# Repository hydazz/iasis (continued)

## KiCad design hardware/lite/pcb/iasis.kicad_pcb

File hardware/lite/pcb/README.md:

# Iasis board

KiCad 10 project for the six-layer, 133 × 102 mm Iasis board. One layout carries three assembly variants, Hub, HubPD and CM5; the [repository README](../../../README.md) describes them.

## Files

- `iasis.kicad_sch` and its sheets, `iasis.kicad_pcb`, `iasis.kicad_pro`, and `iasis.kicad_dru` for the rules the board setup cannot express.
- `Iasis.kicad_sym`, `Iasis.pretty` and `Iasis.3dshapes`: project symbols, footprints and models. `NOTICE` files give their sources and licences.
- `jlc_cpl.py` corrects placements for JLCPCB (below); `preview.py` writes `preview/board.png` and `preview/layout.png`; `diff.py` shows a board change (below).

## Fab files

Tools come from mise (`mise install` at the repository root); KiCad 10 must be at the path `KICAD_CLI` names in `.mise/config.toml`.

```bash
mise run //hardware/lite/pcb:fab
```

The task writes `build/`:

| File                           | Contents                                                  |
| ------------------------------ | --------------------------------------------------------- |
| `gerbers.zip`                  | Gerber and drill files                                    |
| `bom-Hub.csv`, `bom-HubPD.csv`, `bom-CM5.csv` | Bill of materials per variant, one row per LCSC part      |
| `cpl-Hub.csv`, `cpl-HubPD.csv`, `cpl-CM5.csv` | Placements per variant, corrected for JLCPCB's footprints |

Run `mise run //hardware/lite/pcb:preview` to refresh the tracked board and copper-layout images. Commit them with the design changes they show.

Run `mise run //hardware/lite/pcb:step` to export `build/board.step`, which the case tasks consume. Run `mise run //hardware/lite/pcb:check` for DRC with schematic parity and ERC errors; reports are written to `build/drc.json` and `build/erc.json`.

The upload ZIP contains Gerber and drill files. It excludes the optional Gerber job file, whose board-preview colour and impedance-control metadata differ from the order settings below.

The underside carries the name, repository URL and `REV ${REVISION}`, read from the board's title block. The PCB revision identifies a fabricated board design; tag its source commit (for example, `hw-rev-a`) and keep that release's fabrication files together. All three assembly variants share the PCB revision.

### Logo

Supply a filled SVG to place a logo on the back silkscreen:

```bash
mise run //hardware/lite/pcb:fab -- --logo ../../../logos/logo.svg
```

The logo fits within a 45 × 45 mm slot centred 82 mm from the left and 42.5 mm from the top, viewed from below. Its proportions and viewing orientation are preserved. Use solid filled paths; convert text and strokes to paths before exporting the SVG. KiCad's bundled Python, selected by `KICAD_PYTHON`, handles the import.

Without `--logo`, the board has only its identity text. The source board is never modified. Outputs include a board copy, project settings and `bottom.svg` alongside the fabrication files. Use `--output DIR` to change the output directory.

The root `logos/` directory holds local SVG inputs and ignores them by default. A logo can also be supplied from any other path.

## Visual diff

```bash
mise run //hardware/lite/pcb:diff
```

compares the last commit's board with the working copy; `diff REV` compares a revision with the working copy, and `diff OLD NEW` two revisions. The task plots each copper, silkscreen and courtyard layer and the outline of both boards, without zone fills, and draws what was removed red, what was added green and the rest grey. It opens `build/diff/index.html`, which pans and zooms each layer and counts the tracks, vias and footprints that changed.

## JLCPCB order

PCB options:

| Option                  | Setting                 | Reason                                                                                                        |
| ----------------------- | ----------------------- | ------------------------------------------------------------------------------------------------------------- |
| Layers, size            | 6, 133 × 102 mm          |                                                                                                               |
| Thickness               | 1.6 mm                  | Economic assembly of six layers needs 1.6 mm, green and ENIG                                                  |
| Specify stackup         | JLC06161H-3313          | The 90 Ω pairs (0.1356 mm tracks, 0.1501 mm gap) are sized for it; accept JLC's 1.54 mm actual thickness note |
| Colour                  | Green                   | As thickness                                                                                                  |
| Surface finish          | ENIG                    | As thickness. JLC preselects OSP, which rules out Economic assembly, and has no HASL                          |
| Via covering            | Epoxy filled and capped | No charge on six layers; some vias sit in pads                                                                |
| Min via hole / diameter | 0.3 / (0.4/0.45) mm     | No hole is smaller; 0.2 mm holes add a small-via charge and force TG155 and a 4-wire Kelvin test              |
| Impedance control       | No requirement          | ±10 % control adds a charge and requires production-file confirmation                                         |
| Mark on PCB             | Remove mark             |                                                                                                               |

Assembly options: Economic PCBA, top side, tooling holes added by JLCPCB, Confirm Parts Placement on (JLC confirms on its own after 72 hours unless "Do not confirm automatically" is ticked), parts selected by customer. PCBA quantity can be 2 or all 5 boards.

Upload `gerbers.zip`, then the variant's BOM and CPL, and:

1. Tick the USB-C rows (J1001, J401–J901). JLC charges a small fee for these parts and leaves them unticked after every upload.
2. Check every row is matched, in stock and selectable; Economic cannot place a part JLC marks Standard Only. Replace such a part in the schematic and regenerate the files, rather than in JLC's table, so the BOM here stays the order's source.
3. In Component Placements, every part should sit on its pads, and JLC's Align should change nothing. A part that Align turns or moves needs an entry in `jlc_cpl.py`.
4. The closest customs description is Research/Education/DIY, Development Board (HS 847330).

## Placement corrections

JLCPCB places its own (EasyEDA) footprint for each LCSC part, with its origin at the CPL's Mid X/Y and turned by Rotation. `jlc_cpl.py` holds, by LCSC code, the turn to add and the EasyEDA origin's position in the KiCad footprint, wherever the two footprints differ.

For a new part, fetch its EasyEDA footprint from `https://easyeda.com/api/products/<LCSC>/components?version=6.4.19.5` (pads in 0.254 mm units, y down, origin at `dataStr.head`). Match its pads to the KiCad pads by number at each quarter turn, then record the turn and origin that fit. Two-terminal chip parts need no entry.

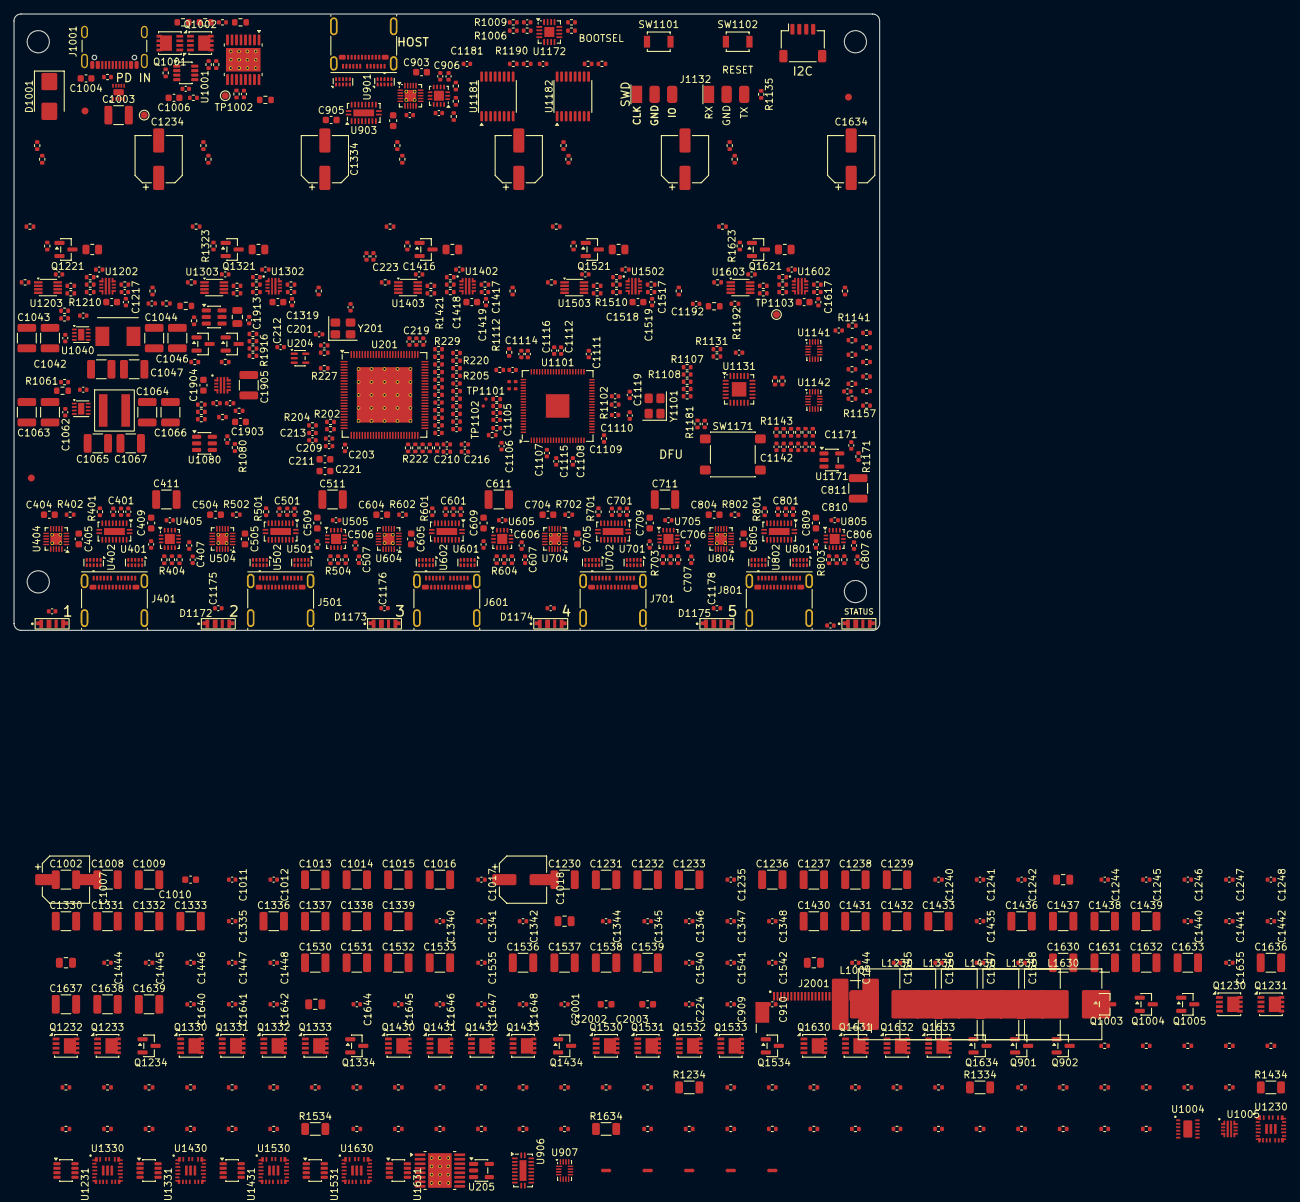
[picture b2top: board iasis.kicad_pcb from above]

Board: 6 copper layers, 125.0 x 89.0 mm, 718 parts (0 on the bottom side), 493 nets, no tracks yet.

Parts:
C201, C202, C1012: 33p C0G; C_0402_1005Metric
C203, C204, C205, C206, C207, C208, C209, C210, C212, C213, C214, C215, C216, C217, C218, C219, C220, C224, C226, C403, C408, C410, C503, C508, C510, C603, C608, C610, C703, C708, C710, C803, C808, C810, C904, C908, C909, C910, C1011, C1041, C1061, C1080, C1104, C1105, C1106, C1107, C1108, C1109, C1110, C1111, C1112, C1113, C1114, C1115, C1116, C1131, C1141, C1147, C1170, C1171, C1172, C1173, C1174, C1175, C1176, C1177, C1178, C1181, C1182, C1216, C1241, C1242, C1316, C1341, C1342, C1416, C1441, C1442, C1516, C1541, C1542, C1616, C1641, C1642, C1906, C1911, C1913: 100n; C_0402_1005Metric
C211, C221: 10u 10V; C_0603_1608Metric
C222, C223: 100n 16V X7R; C_0402_1005Metric
C401, C402, C501, C502, C601, C602, C701, C702, C801, C802: 100n 25V X7R; C_0402_1005Metric
C404, C409, C504, C509, C604, C609, C704, C709, C804, C809, C902, C905: 1u 10V X7R; C_0603_1608Metric
C405, C505, C605, C705, C805, C903: 100n 50V X7R; C_0603_1608Metric
C406, C407, C506, C507, C606, C607, C706, C707, C806, C807, C906, C907, C1060: 220p C0G; C_0402_1005Metric
C411, C511, C611, C711, C811, C1013, C1014, C1015, C1016, C1042, C1043, C1044, C1045, C1046, C1047, C1062, C1063, C1064, C1065, C1066, C1067, C1905: 22u 16V X7R; C_1210_3225Metric
C1001, C1005, C1219, C1220, C1235, C1240, C1247, C1248, C1319, C1320, C1335, C1340, C1347, C1348, C1419, C1420, C1435, C1440, C1447, C1448, C1519, C1520, C1535, C1540, C1547, C1548, C1619, C1620, C1635, C1640, C1647, C1648: 100n 50V X7R; C_0402_1005Metric
C1002, C1003, C1008, C1009, C1230, C1231, C1232, C1233, C1236, C1237, C1238, C1239, C1330, C1331, C1332, C1333, C1336, C1337, C1338, C1339, C1430, C1431, C1432, C1433, C1436, C1437, C1438, C1439, C1530, C1531, C1532, C1533, C1536, C1537, C1538, C1539, C1630, C1631, C1632, C1633, C1636, C1637, C1638, C1639: 10u 50V X7R; C_1210_3225Metric
C1004, C1010, C2002, C2003: 100n 100V X7R; C_0603_1608Metric
C1006: 22n 100V X7R; C_0603_1608Metric
C1007: 33u 50V; CP_Elec_6.3x7.7
C1017, C1040, C1245, C1345, C1445, C1545, C1645: 4.7n; C_0402_1005Metric
C1018, C1234, C1334, C1434, C1534, C1634: 100u 35V; CP_Elec_6.3x7.7
C1101, C1102: 4.7u 10V X5R; C_0402_1005Metric_WideGap
C1103, C1117: 4.7u 10V X5R; C_0402_1005Metric
C1118, C1119: 15p C0G; C_0402_1005Metric
C1142, C1143, C1144, C1145, C1146, C1148, C1191, C1192, C1244, C1344, C1444, C1544, C1644, C2001: 10n; C_0402_1005Metric
C1217, C1317, C1417, C1517, C1617: 1n 50V C0G; C_0402_1005Metric
C1218, C1318, C1418, C1518, C1618, C1904: 2.2u 25V X5R; C_0603_1608Metric
C1243, C1343, C1443, C1543, C1643, C1912: 10u 16V X5R; C_0805_2012Metric
C1246, C1346, C1446, C1546, C1646: 100p C0G; C_0402_1005Metric
C1903: 47n 50V X7R; C_0603_1608Metric
D1001: SMBJ30CA; D_SMB
D1170, D1171, D1172, D1173, D1174, D1175: SK6812SIDE-A; OPSCO_SK6812SIDE-A
FID1, FID2, FID3: Fiducial; Fiducial_1mm_Mask2mm
H1, H2, H3, H4: MountingHole_3.2mm_M3
J401, J501, J601, J701, J801, J901: 1054500101; USB_C_Receptacle_Molex_105450-0101
J1001: USB4105-GF-A-120; GCT_USB4105_GF_A_120
J1101: SWD debug; SolderPads_1x03_P2.54mm
J1131: SM04B-SRSS-TB; JST_SH_SM04B-SRSS-TB_1x04-1MP_P1.00mm_Horizontal
J1132: UART debug; SolderPads_1x03_P2.54mm
J2001: 05A20L24P; HanElectricity_05A20L24P
L1004: 6.8u 12.5A; PSTMAA666460
L1040: SRP5030CC-2R2M; Bourns_SRP5030CC
L1060: AAPS0530M1R0F; L_Coilank_AAPS0530
L1230, L1330, L1430, L1530, L1630: 4.7u; L_Changjiang_FXL1050
NT1230, NT1330, NT1430, NT1530, NT1630: NetTie_2; NetTie-2_SMD_Pad0.5mm
Q901, Q902, Q1003, Q1004, Q1005, Q1221, Q1234, Q1321, Q1334, Q1421, Q1434, Q1521, Q1534, Q1621, Q1634, Q1911, Q1912: 2N7002; SOT-23
Q1001, Q1002, Q1232, Q1233, Q1332, Q1333, Q1432, Q1433, Q1532, Q1533, Q1632, Q1633: SP60N05GNJ; Vishay_PowerPAK_1212-8_Single
Q1230, Q1231, Q1330, Q1331, Q1430, Q1431, Q1530, Q1531, Q1630, Q1631: TMGN4060DF; Vishay_PowerPAK_1212-8_Single
R201: 12k 1%; R_0402_1005Metric
R202, R1012, R1191, R1192, R1212, R1312, R1412, R1512, R1612, R1907: 10k 1%; R_0402_1005Metric
R203, R204, R205, R206, R232, R1235, R1335, R1435, R1535, R1635, R1913: 200k 1%; R_0402_1005Metric
R207, R208, R209, R210, R211, R212, R213, R214, R215, R401, R402, R403, R501, R502, R503, R601, R602, R603, R701, R702, R703, R801, R802, R803, R901, R907, R1006, R1009, R1015, R1020, R1022, R1024, R1080, R1104, R1112, R1135, R1173, R1181, R1187, R1210, R1310, R1410, R1510, R1610, R1912, R2003, R2005: 10k; R_0402_1005Metric
R217, R218, R219, R220, R221, R222, R223, R224, R225, R226, R227, R228, R229, R230, R231, R904, R906, R1010, R1026, R1029, R1172, R1185, R1188, R1189, R1190, R1209, R1214, R1215, R1221, R1223, R1238, R1239, R1309, R1314, R1315, R1321, R1323, R1338, R1339, R1409, R1414, R1415, R1421, R1423, R1438, R1439, R1509, R1514, R1515, R1521, R1523, R1538, R1539, R1609, R1614, R1615, R1621, R1623, R1638, R1639, R1911, R1915, R1917: 100k; R_0402_1005Metric
R404, R405, R504, R505, R604, R605, R704, R705, R804, R805, R902, R903, R1028, R1107, R1108, R1109, R1110, R1111, R1136, R1137: 4.7k; R_0402_1005Metric
R905: 1M; R_0402_1005Metric
R1001, R1002: 100k 0.1%; R_0603_1608Metric
R1003, R1014, R1021, R1231, R1232, R1236, R1331, R1332, R1336, R1431, R1432, R1436, R1531, R1532, R1536, R1631, R1632, R1636: 47k 1%; R_0402_1005Metric
R1004: 10k 0.1%; R_0603_1608Metric
R1005: 100k 1%; R_0402_1005Metric
R1007: 22; R_0603_1608Metric
R1008, R2002: 6.8k 1%; R_0402_1005Metric
R1011: 249k 1%; R_0402_1005Metric
R1013, R1102, R1103: 1k; R_0402_1005Metric
R1016: 120k 1%; R_0402_1005Metric
R1017, R1916: 22k 1%; R_0402_1005Metric
R1018, R1025, R1909: 1k 1%; R_0402_1005Metric
R1019, R1023, R1211, R1311, R1411, R1511, R1611: 39k 1%; R_0402_1005Metric
R1027, R1908: 20k 1%; R_0402_1005Metric
R1040, R1060, R1142, R1145, R1148, R1151, R1154, R1157: 10k 0.1%; R_0402_1005Metric
R1041: 2.2k 0.1%; R_0402_1005Metric
R1061: 11.3k 0.1%; R_0603_1608Metric
R1101, R1171: 33; R_0402_1005Metric
R1105, R1106: 27; R_0402_1005Metric
R1131, R1132: 2.2k; R_0402_1005Metric
R1141, R1144, R1147, R1150, R1153, R1156: 90.9k 0.1%; R_0402_1005Metric
R1143, R1146, R1149, R1152, R1155, R1158: 47k 0.1%; R_0402_1005Metric
R1213, R1313, R1413, R1513, R1613: 6.49k 1%; R_0402_1005Metric
R1222, R1322, R1422, R1522, R1622: 1k 1%; R_0805_2012Metric
R1230, R1330, R1430, R1530, R1630: 1; R_0402_1005Metric
R1233, R1333, R1433, R1533, R1633: 56k 1%; R_0402_1005Metric
R1234, R1334, R1434, R1534, R1634: 10m 1%; R_1206_3216Metric
R1237, R1337, R1437, R1537, R1637: 15k 1%; R_0402_1005Metric
R1906: 64.9k 0.1%; R_0402_1005Metric
R1910: 100; R_0402_1005Metric
R1914: 68k 1%; R_0402_1005Metric
R2001: 240k 1%; R_0402_1005Metric
R2004: 5.6k 1%; R_0402_1005Metric
SW1101, SW1102: B3U-1000P; SW_SPST_B3U-1000P
SW1171: PTS645SL50SMTR92LFS; SW_SPST_PTS645Sx43SMTR92
TH1191, TH1192: 10k 1% NTC; R_0603_1608Metric
TP1001: CH224_PG_N; TestPoint_Pad_D1.0mm
TP1002: HV_CHARGE; TestPoint_Pad_D1.0mm
TP1101: MCU_USB_D_N; TestPoint_Pad_D0.5mm
TP1102: MCU_USB_D_P; TestPoint_Pad_D0.5mm
TP1103: GND; TestPoint_Pad_D1.0mm
U201: USB7206CT/KDX; VQFN-100-1EP_12x12mm_P0.4mm_EP8x8mm_ThermalVias
U204: SN74AUP1G08DCKR; SOT-353_SC-70-5
U205: SN74LVC1G32DBVR; SOT-23-5
U401, U501, U601, U701, U801, U903, U906: HD3SS3212IRKSR; DHVQFN-20-1EP_2.5x4.5mm_P0.5mm_EP1x3mm
U402, U403, U502, U503, U602, U603, U702, U703, U802, U803, U901, U902: TPD4E02B04DQAR; USON-10_2.5x1.0mm_P0.5mm
U404, U504, U604, U704, U804, U904: TPD6S300ARUKR; WQFN-20-1EP_3x3mm_P0.4mm_EP1.7x1.7mm_ThermalVias
U405, U505, U605, U705, U805, U905: FUSB302BMPX; WQFN-14-1EP_2.5x2.5mm_P0.5mm_EP1.45x1.45mm
U907, U1141, U1142: TMUX1511RSVR; UQFN-16_1.8x2.6mm_P0.4mm
U1001, U1231, U1331, U1431, U1531, U1631: LM74502DDFR; Texas_DDF0008A_SOT-8_1.6x2.9mm_P0.65mm
U1002: CH224Q; WCH_CH224Q_DFN10
U1003, U2001: TPS26600PWPR; HTSSOP-16-1EP_4.4x5mm_P0.65mm_EP3.4x5mm_Mask2.66x2.46mm_The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
U1004: LMR51450SDRRR; TI_DRR0012G
U1005, U1202, U1302, U1402, U1502, U1602, U1902: TPS259470ARPWR; TI_RPW0010A
U1040, U1060: AP3441SHE-7B; DFN-8-1EP_2x2mm_P0.5mm_EP0.9x1.7mm
U1080: TPS3808G33DBVR; SOT-23-6
U1101: RP2354B; QFN-80-1EP_10x10mm_P0.4mm_EP3.4x3.4mm
U1131: TCA9548ARGER; Texas_RGE0024C_VQFN-24-1EP_4x4mm_P0.5mm_EP2.1x2.1mm
U1171: SN74AHCT1G125DBVR; SOT-23-5
U1172: TCA6408ARGTR; VQFN-16-1EP_3x3mm_P0.5mm_EP1.45x1.45mm
U1181, U1182: 74HC595PW; TSSOP-16_4.4x5mm_P0.65mm
U1203, U1303, U1403, U1503, U1603: 74LVC2G08DC-Q100H; VSSOP-8_2.3x2mm_P0.5mm
U1230, U1330, U1430, U1530, U1630: TPS55288RPMR; TI_RPM0026A
U1901: AP22653W6-7; SOT-23-6
Y201: X322525MSB4SI; Crystal_SMD_3225-4Pin_3.2x2.5mm
Y1101: ABM8-272-T3; Crystal_SMD_3225-4Pin_3.2x2.5mm

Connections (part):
3V3_AON: C203.1, C204.1, C205.1, C206.1, C207.1, C208.1, C209.1, C210.1, C211.1, C224.1, C226.1, C403.1, C404.1, C408.1, C409.1, C503.1, C504.1, C508.1, C509.1, C603.1, C604.1, C608.1, C609.1, C703.1, C704.1, C708.1, C709.1, C803.1, C804.1, C808.1, C809.1, C902.1, C904.1, C905.1, C908.1, C909.1, C910.1, C1040.1, C1044.1, C1045.1, C1046.1, C1047.1, C1080.1, C1101.1, C1104.1, C1105.1, C1106.1, C1107.1, C1108.1, C1109.1, C1110.1, C1111.1, C1112.1, C1113.1, C1114.1, C1131.1, C1141.1, C1147.1, C1172.1, C1181.1, C1182.1, C1216.1, C1316.1, C1416.1, C1516.1, C1616.1, J1131.2, L1040.2, R207.1, R208.1, R209.1, R210.1, R211.1, R212.1, R213.1, R214.1, R215.1, R401.1, R402.1, R403.1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
5V_LOGIC: C410.1, C411.1, C510.1, C511.1, C610.1, C611.1, C710.1, C711.1, C810.1, C811.1, C1018.1, C1041.1, C1042.1, C1043.1, C1061.1, C1062.1, C1063.1, C1170.1, C1171.1, C1174.1, C1175.1, C1176.1, C1177.1, C1178.1, C1905.1, C1906.1, C1911.1, D1170.2 (VDD), D1171.2 (VDD), D1172.2 (VDD), D1173.2 (VDD), D1174.2 (VDD), D1175.2 (VDD), R1026.1, R1230.1, R1330.1, R1430.1, R1530.1, R1630.1, U405.12 (VCONN), U405.13 (VCONN), U505.12 (VCONN), U505.13 (VCONN), U605.12 (VCONN), U605.13 (VCONN), U705.12 (VCONN), U705.13 (VCONN), U805.12 (VCONN), U805.13 (VCONN), U1005.6 (OUT), U1040.3 (VIN), U1040.7 (EN), U1060.3 (VIN), U1171.5 (VCC), U1901.1 (IN), U1902.6 (OUT)
/Brick input and logic child/AUXOFF: Q1004.1 (G), R1026.2, U1005.3 (AUXOFF)
/Brick input and logic child/CH_SUPPLY: C1003.1, R1007.2, U1002.1 (VHV), U1002.8 (VBUS)
/Brick input and logic child/INPUT_PROTECT_DVDT: C1001.1, U1003.12 (dVdT)
/Brick input and logic child/INPUT_PROTECT_ILIM: R1005.1, U1003.11 (ILIM)
/Brick input and logic child/INPUT_PROTECT_OVP: R1003.2, R1004.1, U1003.5 (OVP)
/Brick input and logic child/LOGIC_5V2: C1012.1, C1013.1, C1014.1, C1015.1, C1016.1, L1004.2, R1016.1, R1023.1, U1005.5 (IN)
/Brick input and logic child/LOGIC_BUCK_EN: R1019.2, R1020.1, U1004.9 (EN)
/Brick input and logic child/LOGIC_FB: R1016.2, R1017.1, R1018.2, U1004.7 (FB)
/Brick input and logic child/LOGIC_PRI_DVDT: C1017.1, U1005.7 (DVDT)
/Brick input and logic child/LOGIC_PRI_EN: R1021.2, R1022.1, U1005.1 (EN_UVLO)
/Brick input and logic child/LOGIC_PRI_ILM: R1025.1, U1005.9 (ILM)
/Brick input and logic child/LOGIC_PRI_OVLO: R1023.2, R1024.1, U1005.2 (OVLO)
/Brick input and logic child/PD_CC1: J1001.A5 (CC1), U1002.7 (CC1)
/Brick input and logic child/PD_CC2: J1001.B5 (CC2), U1002.6 (CC2)
/Brick input and logic child/PD_CFG1: R1008.1, U1002.9 (CFG1)
/Brick input and logic child/PD_EN: Q1003.3 (D), R1014.2, R1015.1, U1001.1 (EN)
/Brick input and logic child/PD_GATE: C1006.1, Q1001.4 (G), Q1002.4 (G), U1001.6 (GATE)
/Brick input and logic child/PD_OV: R1011.2, R1012.1, U1001.7 (OV)
/Brick input and logic child/PD_SRC: Q1001.1 (S), Q1001.2 (S), Q1001.3 (S), Q1002.1 (S), Q1002.2 (S), Q1002.3 (S), U1001.8 (SRC)
/Brick input and logic child/PD_VBUS_RAW: C1004.1, C1005.2, D1001.1 (A1), J1001.A4 (VBUS), J1001.A9 (VBUS), J1001.B4 (VBUS), J1001.B9 (VBUS), Q1001.5 (D), R1001.1, R1011.1, R1014.1, U1001.5 (VS), U1003.1 (IN), U1003.2 (IN), U1003.3 (UVLO)
/Brick input and logic child/PD_VCAP: C1005.1, U1001.4 (VCAP)
/Host port/CC1_CONN: J901.A5 (CC1), U904.4 (C_CC1), U904.7 (RPD_G1)
/Host port/CC1_PD: C906.1, U904.12 (CC1), U905.10 (CC1), U905.11 (CC1)
/Host port/CC2_CONN: J901.B5 (CC2), U904.5 (C_CC2), U904.6 (RPD_G2)
/Host port/CC2_PD: C907.1, U904.11 (CC2), U905.1 (CC2), U905.14 (CC2)
/Host port/CM5_HOST_N: Q901.3 (D), R904.2, U907.11 (SEL3), U907.15 (SEL4)
/Host port/D_CONN_N: J901.A7 (D-), J901.B7 (D-), U904.2 (C_SBU2)
/Host port/D_CONN_P: J901.A6 (D+), J901.B6 (D+), U904.1 (C_SBU1)
/Host port/EXT_PD_INT_N: R901.2, U905.5 (INT_N)
/Host port/RX1_N: J901.B10 (RX1-), U901.5 (D2-), U901.6 (NC), U903.12 (C1N)
/Host port/RX1_P: J901.B11 (RX1+), U901.4 (D2+), U901.7 (NC), U903.13 (C1P)
/Host port/RX2_N: J901.A10 (RX2-), U902.5 (D2-), U902.6 (NC), U903.16 (B1N)
/Host port/RX2_P: J901.A11 (RX2+), U902.4 (D2+), U902.7 (NC), U903.17 (B1P)
/Host port/TX1_N: J901.A2 (TX1+), U901.2 (D1-), U901.9 (NC), U903.14 (C0N)
/Host port/TX1_P: J901.A3 (TX1-), U901.1 (D1+), U901.10 (NC), U903.15 (C0P)
/Host port/TX2_N: J901.B2 (TX2+), U902.2 (D1-), U902.9 (NC), U903.18 (B0N)
/Host port/TX2_P: J901.B3 (TX2-), U902.1 (D1+), U902.10 (NC), U903.19 (B0P)
/Host port/VBIAS: C903.1, U904.3 (VBIAS)
/Host power and target budget/HOST_BUDGET_ILIM: R1913.1, R1914.1, R1916.1, U1901.5 (ILIM)
/Host power and target budget/LOGIC_DVDT: R1910.1, U1902.7 (DVDT)
/Host power and target budget/LOGIC_EN: R1906.2, R1907.1, U1902.1 (EN_UVLO)
/Host power and target budget/LOGIC_ILIM: R1909.1, U1902.9 (ILM)
/Indicators and confirmation/LED_DIN0: D1170.1 (DIN), R1171.2
/Indicators and confirmation/LED_DIN1: D1170.3 (DOUT), D1175.1 (DIN)
/Indicators and confirmation/LED_DIN2: D1174.1 (DIN), D1175.3 (DOUT)
/Indicators and confirmation/LED_DIN3: D1173.1 (DIN), D1174.3 (DOUT)
/Indicators and confirmation/LED_DIN4: D1172.1 (DIN), D1173.3 (DOUT)
/Indicators and confirmation/LED_DIN5: D1171.1 (DIN), D1172.3 (DOUT)
/Indicators and confirmation/LED_DRIVE: R1171.1, U1171.4
/Logic supplies and reset/FB_1040: C1040.2, R1040.2, R1041.1, U1040.1 (FB)
/Logic supplies and reset/FB_1060: C1060.2, R1060.2, R1061.1, U1060.1 (FB)
/Logic supplies and reset/LX_1040: L1040.1, U1040.6 (LX)
/Logic supplies and reset/LX_1060: L1060.1, U1060.6 (LX)
/Port voltage measurement/LOCAL_P1_DIV: R1141.2, R1142.1, U1141.2 (S1)
/Port voltage measurement/LOCAL_P2_DIV: R1144.2, R1145.1, U1141.5 (S2)
/Port voltage measurement/LOCAL_P3_DIV: R1147.2, R1148.1, U1141.10 (S3)
/Port voltage measurement/LOCAL_P4_DIV: R1150.2, R1151.1, U1141.14 (S4)
/Port voltage measurement/LOCAL_P5_DIV: R1153.2, R1154.1, U1142.2 (S1)
/Port voltage measurement/LOCAL_VSYS_DIV: R1156.2, R1157.1, U1142.5 (S2)
/Power control outputs/SHIFT_CASCADE: U1181.9 (QH'), U1182.14 (SER)
/RP2354 controller/MCU_BOOTSEL_N: R1103.2, SW1101.1
/RP2354 controller/MCU_QSPI_SS_N: R1103.1, R1104.2, U1101.75 (~QSPI_SS)
/RP2354 controller/MCU_SWCLK: J1101.1, U1101.33 (SWCLK)
/RP2354 controller/MCU_SWDIO: J1101.3, U1101.34 (SWDIO)
/RP2354 controller/MCU_USB_D_RAW_N: R1105.1, U1101.66 (USB_DM)
/RP2354 controller/MCU_USB_D_RAW_P: R1106.1, U1101.67 (USB_DP)
/RP2354 controller/MCU_VREG_AVDD: C1103.1, R1101.2, U1101.61 (VREG_AVDD)
/RP2354 controller/MCU_XIN: C1118.1, U1101.30 (XIN), Y1101.1
/RP2354 controller/MCU_XOUT: R1102.1, U1101.31 (XOUT)
/RP2354 controller/MCU_XTAL_OUT: C1119.1, R1102.2, Y1101.3
/Side link/SIDE_BUS: C2003.1, J2001.15, J2001.16, J2001.17, J2001.18, J2001.19, J2001.20, U2001.15 (OUT), U2001.16 (OUT)
/Side link/SIDE_OVP: R2002.2, R2003.1, U2001.5 (OVP)
/Side link/SIDE_UVLO: R2001.2, R2002.1, U2001.3 (UVLO)
/Target ports/Target 1/Output and charging/CHARGE_EN: R1239.1, U1203.3, U1231.1 (EN)
/Target ports/Target 1/Output and charging/HOST_DVDT: C1217.1, U1202.7 (DVDT)
/Target ports/Target 1/Output and charging/HOST_EN: R1215.1, U1202.1 (EN_UVLO), U1203.7
/Target ports/Target 1/Output and charging/HOST_ILIM: R1213.1, U1202.9 (ILM)
/Target ports/Target 1/Output and charging/HOST_OVLO: R1211.2, R1212.1, U1202.2 (OVLO)
/Target ports/Target 1/Output and charging/Optional charging/CONV: C1234.1, C1247.2, C1248.1, Q1232.5 (D), R1234.2, R1235.1, U1230.13 (ISN), U1231.5 (VS)
/Target ports/Target 1/Output and charging/Optional charging/OUT_GATE: Q1232.4 (G), Q1233.4 (G), U1231.6 (GATE)
/Target ports/Target 1/Output and charging/Optional charging/OUT_OV: R1235.2, R1236.1, R1237.1, U1231.7 (OV)
/Target ports/Target 1/Output and charging/Optional charging/OUT_SRC: Q1232.1 (S), Q1232.2 (S), Q1232.3 (S), Q1233.1 (S), Q1233.2 (S), Q1233.3 (S), U1231.8 (SRC)
/Target ports/Target 1/Output and charging/Optional charging/STAGE_AGND: C1244.2, C1245.2, C1246.2, NT1230.2, R1231.2, R1232.2, U1230.10 (AGND)
/Target ports/Target 1/Output and charging/Optional charging/STAGE_COMP: C1246.1, R1233.1, U1230.18 (COMP)
/Target ports/Target 1/Output and charging/Optional charging/STAGE_DITH: C1244.1, U1230.7 (DITH_SYNC)
/Target ports/Target 1/Output and charging/Optional charging/STAGE_FSW: R1231.1, U1230.8 (FSW)
/Target ports/Target 1/Output and charging/Optional charging/STAGE_ILIM: R1232.1, U1230.17 (ILIM)
/Target ports/Target 1/Output and charging/Optional charging/STAGE_VCC: C1243.1, R1230.2, U1230.19 (VCC)
/Target ports/Target 1/Output and charging/Optional charging/STAGE_VOUT: C1236.1, C1237.1, C1238.1, C1239.1, C1240.1, R1234.1, U1230.11 (VOUT), U1230.12 (ISP), U1230.26 (VOUT)
/Target ports/Target 1/Output and charging/Optional charging/SW1: C1241.2, L1230.1, Q1230.1 (S), Q1230.2 (S), Q1230.3 (S), Q1231.5 (D), U1230.23 (SW1)
/Target ports/Target 1/Output and charging/Optional charging/SW2: C1242.2, L1230.2, U1230.21 (SW2), U1230.25 (SW2)
/Target ports/Target 1/USB-C data and PD/CC1_CONN: J401.A5 (CC1), U404.4 (C_CC1)
/Target ports/Target 1/USB-C data and PD/CC1_PD: C406.1, U404.12 (CC1), U405.10 (CC1), U405.11 (CC1)
/Target ports/Target 1/USB-C data and PD/CC2_CONN: J401.B5 (CC2), U404.5 (C_CC2)
/Target ports/Target 1/USB-C data and PD/CC2_PD: C407.1, U404.11 (CC2), U405.1 (CC2), U405.14 (CC2)
/Target ports/Target 1/USB-C data and PD/RX1_N: J401.B10 (RX1-), U401.12 (C1N), U402.5 (D2-), U402.6 (NC)
/Target ports/Target 1/USB-C data and PD/RX1_P: J401.B11 (RX1+), U401.13 (C1P), U402.4 (D2+), U402.7 (NC)
/Target ports/Target 1/USB-C data and PD/RX2_N: J401.A10 (RX2-), U401.16 (B1N), U403.5 (D2-), U403.6 (NC)
/Target ports/Target 1/USB-C data and PD/RX2_P: J401.A11 (RX2+), U401.17 (B1P), U403.4 (D2+), U403.7 (NC)
/Target ports/Target 1/USB-C data and PD/TX1_N: J401.A2 (TX1+), U401.14 (C0N), U402.2 (D1-), U402.9 (NC)
/Target ports/Target 1/USB-C data and PD/TX1_P: J401.A3 (TX1-), U401.15 (C0P), U402.1 (D1+), U402.10 (NC)
/Target ports/Target 1/USB-C data and PD/TX2_N: J401.B2 (TX2+), U401.18 (B0N), U403.2 (D1-), U403.9 (NC)
/Target ports/Target 1/USB-C data and PD/TX2_P: J401.B3 (TX2-), U401.19 (B0P), U403.1 (D1+), U403.10 (NC)
/Target ports/Target 1/USB-C data and PD/TX_N: C402.2, U401.3 (A0P)
/Target ports/Target 1/USB-C data and PD/TX_P: C401.2, U401.4 (A0N)
/Target ports/Target 1/USB-C data and PD/USB2_D_CONN_N: J401.A7 (D-), J401.B7 (D-), U404.2 (C_SBU2)
/Target ports/Target 1/USB-C data and PD/USB2_D_CONN_P: J401.A6 (D+), J401.B6 (D+), U404.1 (C_SBU1)
/Target ports/Target 1/USB-C data and PD/VBIAS: C405.1, U404.3 (VBIAS)
/Target ports/Target 2/Output and charging/CHARGE_EN: R1339.1, U1303.3, U1331.1 (EN)
/Target ports/Target 2/Output and charging/HOST_DVDT: C1317.1, U1302.7 (DVDT)
/Target ports/Target 2/Output and charging/HOST_EN: R1315.1, U1302.1 (EN_UVLO), U1303.7
/Target ports/Target 2/Output and charging/HOST_ILIM: R1313.1, U1302.9 (ILM)
/Target ports/Target 2/Output and charging/HOST_OVLO: R1311.2, R1312.1, U1302.2 (OVLO)
/Target ports/Target 2/Output and charging/Optional charging/CONV: C1334.1, C1347.2, C1348.1, Q1332.5 (D), R1334.2, R1335.1, U1330.13 (ISN), U1331.5 (VS)
/Target ports/Target 2/Output and charging/Optional charging/OUT_GATE: Q1332.4 (G), Q1333.4 (G), U1331.6 (GATE)
/Target ports/Target 2/Output and charging/Optional charging/OUT_OV: R1335.2, R1336.1, R1337.1, U1331.7 (OV)
/Target ports/Target 2/Output and charging/Optional charging/OUT_SRC: Q1332.1 (S), Q1332.2 (S), Q1332.3 (S), Q1333.1 (S), Q1333.2 (S), Q1333.3 (S), U1331.8 (SRC)
/Target ports/Target 2/Output and charging/Optional charging/STAGE_AGND: C1344.2, C1345.2, C1346.2, NT1330.2, R1331.2, R1332.2, U1330.10 (AGND)
/Target ports/Target 2/Output and charging/Optional charging/STAGE_COMP: C1346.1, R1333.1, U1330.18 (COMP)
/Target ports/Target 2/Output and charging/Optional charging/STAGE_DITH: C1344.1, U1330.7 (DITH_SYNC)
/Target ports/Target 2/Output and charging/Optional charging/STAGE_FSW: R1331.1, U1330.8 (FSW)
/Target ports/Target 2/Output and charging/Optional charging/STAGE_ILIM: R1332.1, U1330.17 (ILIM)
/Target ports/Target 2/Output and charging/Optional charging/STAGE_VCC: C1343.1, R1330.2, U1330.19 (VCC)
/Target ports/Target 2/Output and charging/Optional charging/STAGE_VOUT: C1336.1, C1337.1, C1338.1, C1339.1, C1340.1, R1334.1, U1330.11 (VOUT), U1330.12 (ISP), U1330.26 (VOUT)
/Target ports/Target 2/Output and charging/Optional charging/SW1: C1341.2, L1330.1, Q1330.1 (S), Q1330.2 (S), Q1330.3 (S), Q1331.5 (D), U1330.23 (SW1)
/Target ports/Target 2/Output and charging/Optional charging/SW2: C1342.2, L1330.2, U1330.21 (SW2), U1330.25 (SW2)
/Target ports/Target 2/USB-C data and PD/CC1_CONN: J501.A5 (CC1), U504.4 (C_CC1)
/Target ports/Target 2/USB-C data and PD/CC1_PD: C506.1, U504.12 (CC1), U505.10 (CC1), U505.11 (CC1)
/Target ports/Target 2/USB-C data and PD/CC2_CONN: J501.B5 (CC2), U504.5 (C_CC2)
/Target ports/Target 2/USB-C data and PD/CC2_PD: C507.1, U504.11 (CC2), U505.1 (CC2), U505.14 (CC2)
/Target ports/Target 2/USB-C data and PD/RX1_N: J501.B10 (RX1-), U501.12 (C1N), U502.5 (D2-), U502.6 (NC)
/Target ports/Target 2/USB-C data and PD/RX1_P: J501.B11 (RX1+), U501.13 (C1P), U502.4 (D2+), U502.7 (NC)
/Target ports/Target 2/USB-C data and PD/RX2_N: J501.A10 (RX2-), U501.16 (B1N), U503.5 (D2-), U503.6 (NC)
/Target ports/Target 2/USB-C data and PD/RX2_P: J501.A11 (RX2+), U501.17 (B1P), U503.4 (D2+), U503.7 (NC)
/Target ports/Target 2/USB-C data and PD/TX1_N: J501.A2 (TX1+), U501.14 (C0N), U502.2 (D1-), U502.9 (NC)
/Target ports/Target 2/USB-C data and PD/TX1_P: J501.A3 (TX1-), U501.15 (C0P), U502.1 (D1+), U502.10 (NC)
/Target ports/Target 2/USB-C data and PD/TX2_N: J501.B2 (TX2+), U501.18 (B0N), U503.2 (D1-), U503.9 (NC)
/Target ports/Target 2/USB-C data and PD/TX2_P: J501.B3 (TX2-), U501.19 (B0P), U503.1 (D1+), U503.10 (NC)
/Target ports/Target 2/USB-C data and PD/TX_N: C502.2, U501.3 (A0P)
/Target ports/Target 2/USB-C data and PD/TX_P: C501.2, U501.4 (A0N)
/Target ports/Target 2/USB-C data and PD/USB2_D_CONN_N: J501.A7 (D-), J501.B7 (D-), U504.2 (C_SBU2)
/Target ports/Target 2/USB-C data and PD/USB2_D_CONN_P: J501.A6 (D+), J501.B6 (D+), U504.1 (C_SBU1)
/Target ports/Target 2/USB-C data and PD/VBIAS: C505.1, U504.3 (VBIAS)
/Target ports/Target 3/Output and charging/CHARGE_EN: R1439.1, U1403.3, U1431.1 (EN)
/Target ports/Target 3/Output and charging/HOST_DVDT: C1417.1, U1402.7 (DVDT)
/Target ports/Target 3/Output and charging/HOST_EN: R1415.1, U1402.1 (EN_UVLO), U1403.7
/Target ports/Target 3/Output and charging/HOST_ILIM: R1413.1, U1402.9 (ILM)
/Target ports/Target 3/Output and charging/HOST_OVLO: R1411.2, R1412.1, U1402.2 (OVLO)
/Target ports/Target 3/Output and charging/Optional charging/CONV: C1434.1, C1447.2, C1448.1, Q1432.5 (D), R1434.2, R1435.1, U1430.13 (ISN), U1431.5 (VS)
/Target ports/Target 3/Output and charging/Optional charging/OUT_GATE: Q1432.4 (G), Q1433.4 (G), U1431.6 (GATE)
/Target ports/Target 3/Output and charging/Optional charging/OUT_OV: R1435.2, R1436.1, R1437.1, U1431.7 (OV)
/Target ports/Target 3/Output and charging/Optional charging/OUT_SRC: Q1432.1 (S), Q1432.2 (S), Q1432.3 (S), Q1433.1 (S), Q1433.2 (S), Q1433.3 (S), U1431.8 (SRC)
/Target ports/Target 3/Output and charging/Optional charging/STAGE_AGND: C1444.2, C1445.2, C1446.2, NT1430.2, R1431.2, R1432.2, U1430.10 (AGND)
/Target ports/Target 3/Output and charging/Optional charging/STAGE_COMP: C1446.1, R1433.1, U1430.18 (COMP)
/Target ports/Target 3/Output and charging/Optional charging/STAGE_DITH: C1444.1, U1430.7 (DITH_SYNC)
/Target ports/Target 3/Output and charging/Optional charging/STAGE_FSW: R1431.1, U1430.8 (FSW)
/Target ports/Target 3/Output and charging/Optional charging/STAGE_ILIM: R1432.1, U1430.17 (ILIM)
/Target ports/Target 3/Output and charging/Optional charging/STAGE_VCC: C1443.1, R1430.2, U1430.19 (VCC)
/Target ports/Target 3/Output and charging/Optional charging/STAGE_VOUT: C1436.1, C1437.1, C1438.1, C1439.1, C1440.1, R1434.1, U1430.11 (VOUT), U1430.12 (ISP), U1430.26 (VOUT)
/Target ports/Target 3/Output and charging/Optional charging/SW1: C1441.2, L1430.1, Q1430.1 (S), Q1430.2 (S), Q1430.3 (S), Q1431.5 (D), U1430.23 (SW1)
/Target ports/Target 3/Output and charging/Optional charging/SW2: C1442.2, L1430.2, U1430.21 (SW2), U1430.25 (SW2)
/Target ports/Target 3/USB-C data and PD/CC1_CONN: J601.A5 (CC1), U604.4 (C_CC1)
/Target ports/Target 3/USB-C data and PD/CC1_PD: C606.1, U604.12 (CC1), U605.10 (CC1), U605.11 (CC1)
/Target ports/Target 3/USB-C data and PD/CC2_CONN: J601.B5 (CC2), U604.5 (C_CC2)
/Target ports/Target 3/USB-C data and PD/CC2_PD: C607.1, U604.11 (CC2), U605.1 (CC2), U605.14 (CC2)
/Target ports/Target 3/USB-C data and PD/RX1_N: J601.B10 (RX1-), U601.12 (C1N), U602.5 (D2-), U602.6 (NC)
/Target ports/Target 3/USB-C data and PD/RX1_P: J601.B11 (RX1+), U601.13 (C1P), U602.4 (D2+), U602.7 (NC)
/Target ports/Target 3/USB-C data and PD/RX2_N: J601.A10 (RX2-), U601.16 (B1N), U603.5 (D2-), U603.6 (NC)
/Target ports/Target 3/USB-C data and PD/RX2_P: J601.A11 (RX2+), U601.17 (B1P), U603.4 (D2+), U603.7 (NC)
/Target ports/Target 3/USB-C data and PD/TX1_N: J601.A2 (TX1+), U601.14 (C0N), U602.2 (D1-), U602.9 (NC)
/Target ports/Target 3/USB-C data and PD/TX1_P: J601.A3 (TX1-), U601.15 (C0P), U602.1 (D1+), U602.10 (NC)
/Target ports/Target 3/USB-C data and PD/TX2_N: J601.B2 (TX2+), U601.18 (B0N), U603.2 (D1-), U603.9 (NC)
/Target ports/Target 3/USB-C data and PD/TX2_P: J601.B3 (TX2-), U601.19 (B0P), U603.1 (D1+), U603.10 (NC)
/Target ports/Target 3/USB-C data and PD/TX_N: C602.2, U601.3 (A0P)
/Target ports/Target 3/USB-C data and PD/TX_P: C601.2, U601.4 (A0N)
/Target ports/Target 3/USB-C data and PD/USB2_D_CONN_N: J601.A7 (D-), J601.B7 (D-), U604.2 (C_SBU2)
/Target ports/Target 3/USB-C data and PD/USB2_D_CONN_P: J601.A6 (D+), J601.B6 (D+), U604.1 (C_SBU1)
/Target ports/Target 3/USB-C data and PD/VBIAS: C605.1, U604.3 (VBIAS)
/Target ports/Target 4/Output and charging/CHARGE_EN: R1539.1, U1503.3, U1531.1 (EN)
/Target ports/Target 4/Output and charging/HOST_DVDT: C1517.1, U1502.7 (DVDT)
/Target ports/Target 4/Output and charging/HOST_EN: R1515.1, U1502.1 (EN_UVLO), U1503.7
/Target ports/Target 4/Output and charging/HOST_ILIM: R1513.1, U1502.9 (ILM)
/Target ports/Target 4/Output and charging/HOST_OVLO: R1511.2, R1512.1, U1502.2 (OVLO)
/Target ports/Target 4/Output and charging/Optional charging/CONV: C1534.1, C1547.2, C1548.1, Q1532.5 (D), R1534.2, R1535.1, U1530.13 (ISN), U1531.5 (VS)
/Target ports/Target 4/Output and charging/Optional charging/OUT_GATE: Q1532.4 (G), Q1533.4 (G), U1531.6 (GATE)
/Target ports/Target 4/Output and charging/Optional charging/OUT_OV: R1535.2, R1536.1, R1537.1, U1531.7 (OV)
/Target ports/Target 4/Output and charging/Optional charging/OUT_SRC: Q1532.1 (S), Q1532.2 (S), Q1532.3 (S), Q1533.1 (S), Q1533.2 (S), Q1533.3 (S), U1531.8 (SRC)
/Target ports/Target 4/Output and charging/Optional charging/STAGE_AGND: C1544.2, C1545.2, C1546.2, NT1530.2, R1531.2, R1532.2, U1530.10 (AGND)
/Target ports/Target 4/Output and charging/Optional charging/STAGE_COMP: C1546.1, R1533.1, U1530.18 (COMP)
/Target ports/Target 4/Output and charging/Optional charging/STAGE_DITH: C1544.1, U1530.7 (DITH_SYNC)
/Target ports/Target 4/Output and charging/Optional charging/STAGE_FSW: R1531.1, U1530.8 (FSW)
/Target ports/Target 4/Output and charging/Optional charging/STAGE_ILIM: R1532.1, U1530.17 (ILIM)
/Target ports/Target 4/Output and charging/Optional charging/STAGE_VCC: C1543.1, R1530.2, U1530.19 (VCC)
/Target ports/Target 4/Output and charging/Optional charging/STAGE_VOUT: C1536.1, C1537.1, C1538.1, C1539.1, C1540.1, R1534.1, U1530.11 (VOUT), U1530.12 (ISP), U1530.26 (VOUT)
/Target ports/Target 4/Output and charging/Optional charging/SW1: C1541.2, L1530.1, Q1530.1 (S), Q1530.2 (S), Q1530.3 (S), Q1531.5 (D), U1530.23 (SW1)
/Target ports/Target 4/Output and charging/Optional charging/SW2: C1542.2, L1530.2, U1530.21 (SW2), U1530.25 (SW2)
/Target ports/Target 4/USB-C data and PD/CC1_CONN: J701.A5 (CC1), U704.4 (C_CC1)
/Target ports/Target 4/USB-C data and PD/CC1_PD: C706.1, U704.12 (CC1), U705.10 (CC1), U705.11 (CC1)
/Target ports/Target 4/USB-C data and PD/CC2_CONN: J701.B5 (CC2), U704.5 (C_CC2)
/Target ports/Target 4/USB-C data and PD/CC2_PD: C707.1, U704.11 (CC2), U705.1 (CC2), U705.14 (CC2)
/Target ports/Target 4/USB-C data and PD/RX1_N: J701.B10 (RX1-), U701.12 (C1N), U702.5 (D2-), U702.6 (NC)
/Target ports/Target 4/USB-C data and PD/RX1_P: J701.B11 (RX1+), U701.13 (C1P), U702.4 (D2+), U702.7 (NC)
/Target ports/Target 4/USB-C data and PD/RX2_N: J701.A10 (RX2-), U701.16 (B1N), U703.5 (D2-), U703.6 (NC)
/Target ports/Target 4/USB-C data and PD/RX2_P: J701.A11 (RX2+), U701.17 (B1P), U703.4 (D2+), U703.7 (NC)
/Target ports/Target 4/USB-C data and PD/TX1_N: J701.A2 (TX1+), U701.14 (C0N), U702.2 (D1-), U702.9 (NC)
/Target ports/Target 4/USB-C data and PD/TX1_P: J701.A3 (TX1-), U701.15 (C0P), U702.1 (D1+), U702.10 (NC)
/Target ports/Target 4/USB-C data and PD/TX2_N: J701.B2 (TX2+), U701.18 (B0N), U703.2 (D1-), U703.9 (NC)
/Target ports/Target 4/USB-C data and PD/TX2_P: J701.B3 (TX2-), U701.19 (B0P), U703.1 (D1+), U703.10 (NC)
/Target ports/Target 4/USB-C data and PD/TX_N: C702.2, U701.3 (A0P)
/Target ports/Target 4/USB-C data and PD/TX_P: C701.2, U701.4 (A0N)
/Target ports/Target 4/USB-C data and PD/USB2_D_CONN_N: J701.A7 (D-), J701.B7 (D-), U704.2 (C_SBU2)
/Target ports/Target 4/USB-C data and PD/USB2_D_CONN_P: J701.A6 (D+), J701.B6 (D+), U704.1 (C_SBU1)
/Target ports/Target 4/USB-C data and PD/VBIAS: C705.1, U704.3 (VBIAS)
/Target ports/Target 5/Output and charging/CHARGE_EN: R1639.1, U1603.3, U1631.1 (EN)
/Target ports/Target 5/Output and charging/HOST_DVDT: C1617.1, U1602.7 (DVDT)
/Target ports/Target 5/Output and charging/HOST_EN: R1615.1, U1602.1 (EN_UVLO), U1603.7
/Target ports/Target 5/Output and charging/HOST_ILIM: R1613.1, U1602.9 (ILM)
/Target ports/Target 5/Output and charging/HOST_OVLO: R1611.2, R1612.1, U1602.2 (OVLO)
/Target ports/Target 5/Output and charging/Optional charging/CONV: C1634.1, C1647.2, C1648.1, Q1632.5 (D), R1634.2, R1635.1, U1630.13 (ISN), U1631.5 (VS)
/Target ports/Target 5/Output and charging/Optional charging/OUT_GATE: Q1632.4 (G), Q1633.4 (G), U1631.6 (GATE)
/Target ports/Target 5/Output and charging/Optional charging/OUT_OV: R1635.2, R1636.1, R1637.1, U1631.7 (OV)
/Target ports/Target 5/Output and charging/Optional charging/OUT_SRC: Q1632.1 (S), Q1632.2 (S), Q1632.3 (S), Q1633.1 (S), Q1633.2 (S), Q1633.3 (S), U1631.8 (SRC)
/Target ports/Target 5/Output and charging/Optional charging/STAGE_AGND: C1644.2, C1645.2, C1646.2, NT1630.2, R1631.2, R1632.2, U1630.10 (AGND)
/Target ports/Target 5/Output and charging/Optional charging/STAGE_COMP: C1646.1, R1633.1, U1630.18 (COMP)
/Target ports/Target 5/Output and charging/Optional charging/STAGE_DITH: C1644.1, U1630.7 (DITH_SYNC)
/Target ports/Target 5/Output and charging/Optional charging/STAGE_FSW: R1631.1, U1630.8 (FSW)
/Target ports/Target 5/Output and charging/Optional charging/STAGE_ILIM: R1632.1, U1630.17 (ILIM)
/Target ports/Target 5/Output and charging/Optional charging/STAGE_VCC: C1643.1, R1630.2, U1630.19 (VCC)
/Target ports/Target 5/Output and charging/Optional charging/STAGE_VOUT: C1636.1, C1637.1, C1638.1, C1639.1, C1640.1, R1634.1, U1630.11 (VOUT), U1630.12 (ISP), U1630.26 (VOUT)
/Target ports/Target 5/Output and charging/Optional charging/SW1: C1641.2, L1630.1, Q1630.1 (S), Q1630.2 (S), Q1630.3 (S), Q1631.5 (D), U1630.23 (SW1)
/Target ports/Target 5/Output and charging/Optional charging/SW2: C1642.2, L1630.2, U1630.21 (SW2), U1630.25 (SW2)
/Target ports/Target 5/USB-C data and PD/CC1_CONN: J801.A5 (CC1), U804.4 (C_CC1)
/Target ports/Target 5/USB-C data and PD/CC1_PD: C806.1, U804.12 (CC1), U805.10 (CC1), U805.11 (CC1)
/Target ports/Target 5/USB-C data and PD/CC2_CONN: J801.B5 (CC2), U804.5 (C_CC2)
/Target ports/Target 5/USB-C data and PD/CC2_PD: C807.1, U804.11 (CC2), U805.1 (CC2), U805.14 (CC2)
/Target ports/Target 5/USB-C data and PD/RX1_N: J801.B10 (RX1-), U801.12 (C1N), U802.5 (D2-), U802.6 (NC)
/Target ports/Target 5/USB-C data and PD/RX1_P: J801.B11 (RX1+), U801.13 (C1P), U802.4 (D2+), U802.7 (NC)
/Target ports/Target 5/USB-C data and PD/RX2_N: J801.A10 (RX2-), U801.16 (B1N), U803.5 (D2-), U803.6 (NC)
/Target ports/Target 5/USB-C data and PD/RX2_P: J801.A11 (RX2+), U801.17 (B1P), U803.4 (D2+), U803.7 (NC)
/Target ports/Target 5/USB-C data and PD/TX1_N: J801.A2 (TX1+), U801.14 (C0N), U802.2 (D1-), U802.9 (NC)
/Target ports/Target 5/USB-C data and PD/TX1_P: J801.A3 (TX1-), U801.15 (C0P), U802.1 (D1+), U802.10 (NC)
/Target ports/Target 5/USB-C data and PD/TX2_N: J801.B2 (TX2+), U801.18 (B0N), U803.2 (D1-), U803.9 (NC)
/Target ports/Target 5/USB-C data and PD/TX2_P: J801.B3 (TX2-), U801.19 (B0P), U803.1 (D1+), U803.10 (NC)
/Target ports/Target 5/USB-C data and PD/TX_N: C802.2, U801.3 (A0P)
/Target ports/Target 5/USB-C data and PD/TX_P: C801.2, U801.4 (A0N)
/Target ports/Target 5/USB-C data and PD/USB2_D_CONN_N: J801.A7 (D-), J801.B7 (D-), U804.2 (C_SBU2)
/Target ports/Target 5/USB-C data and PD/USB2_D_CONN_P: J801.A6 (D+), J801.B6 (D+), U804.1 (C_SBU1)
/Target ports/Target 5/USB-C data and PD/VBIAS: C805.1, U804.3 (VBIAS)
/USB hub — ports 1–5/CFG_BC_EN: R206.1, U201.70 (SPI_D0/CFG_BC_EN/PF22)
/USB hub — ports 1–5/CFG_NON_REM: R205.1, U201.69 (SPI_CE_N/CFG_NON_REM/PF20)
/USB hub — ports 1–5/CFG_STRAP1: R202.1, U201.21 (CFG_STRAP1)
/USB hub — ports 1–5/CFG_STRAP2: R203.1, U201.22 (CFG_STRAP2)
/USB hub — ports 1–5/CFG_STRAP3: R204.1, U201.23 (CFG_STRAP3)
/USB hub — ports 1–5/HUB_RESET_N: U201.1 (RESET_N), U204.4
/USB hub — ports 1–5/PF3: R221.1, U201.44 (PF3/I2S_SDI)
/USB hub — ports 1–5/PF4: R222.1, U201.45 (PF4/I2S_SDO)
/USB hub — ports 1–5/PF5: R223.1, U201.46 (PF5/I2S_SCK)
/USB hub — ports 1–5/PF6: R224.1, U201.47 (PF6/I2S_LRCK)
/USB hub — ports 1–5/PF7: R225.1, U201.48 (PF7/I2S_MCLK)
/USB hub — ports 1–5/PF18: R226.1, U201.61 (PF18/MSTR_I2C_CLK)
/USB hub — ports 1–5/PF19: R230.1, U201.66 (PF19/MIC_DET)
/USB hub — ports 1–5/PF31: R227.1, U201.3 (PF31/MSTR_I2C_DATA)
/USB hub — ports 1–5/PRT_CTL1: R207.2, U201.60 (PF17/PRT_CTL1)
/USB hub — ports 1–5/PRT_CTL2: R208.2, U201.59 (PF16/PRT_CTL2)
/USB hub — ports 1–5/PRT_CTL3: R209.2, U201.58 (PF15/PRT_CTL3)
/USB hub — ports 1–5/PRT_CTL4: R210.2, U201.57 (PF14/PRT_CTL4)
/USB hub — ports 1–5/PRT_CTL5: R211.2, U201.56 (PF13/PRT_CTL5)
/USB hub — ports 1–5/PRT_CTL6: R212.2, U201.77 (PF28/PRT_CTL6)
/USB hub — ports 1–5/RBIAS: R201.1, U201.100 (RBIAS)
/USB hub — ports 1–5/SPI_CLK: R217.1, U201.68 (SPI_CLK/PF21)
/USB hub — ports 1–5/SPI_D1: R218.1, U201.71 (SPI_D1/PF23)
/USB hub — ports 1–5/SPI_D2: R219.1, U201.72 (SPI_D2/PF24)
/USB hub — ports 1–5/SPI_D3: R220.1, U201.73 (SPI_D3/PF25)
/USB hub — ports 1–5/TEST1: R213.2, U201.63 (TEST1)
/USB hub — ports 1–5/TEST2: R214.2, U201.64 (TEST2)
/USB hub — ports 1–5/TEST3: R215.2, U201.65 (TEST3)
/USB hub — ports 1–5/UP_TX_N: C223.1, U201.91 (USB3UP_TXDP)
/USB hub — ports 1–5/UP_TX_P: C222.1, U201.92 (USB3UP_TXDM)
/USB hub — ports 1–5/XI: C201.1, U201.98 (XTALI/CLK_IN), Y201.1
/USB hub — ports 1–5/XO: C202.1, U201.97 (XTALO), Y201.3
AON_RESET_N: R1080.2, SW1102.1, U204.1, U1080.1 (~RESET), U1101.35 (RUN), U1131.24 (~RESET), U1141.1 (SEL1), U1141.4 (SEL2), U1141.11 (SEL3), U1141.15 (SEL4), U1142.1 (SEL1), U1142.4 (SEL2)
AUX_SCL: J1131.4, R1137.2, U1002.2 (SCL), U1131.17 (SC7)
AUX_SDA: J1131.3, R1136.2, U1002.3 (SDA), U1131.16 (SD7)
CH224_PG_N: R1009.2, TP1001.1 (1_1), U1002.10 (PG_N), U1172.9 (P6)
CM5_HOST: J2001.11, Q901.1 (G), Q902.3 (D), R905.1, U205.2, U906.9 (SEL), U907.1 (SEL1), U907.4 (SEL2)
CONFIRM_N: C1173.1, R1181.2, SW1171.1, U1101.21 (GPIO21)
EXP_RESET_N: R1172.1, U1101.40 (GPIO32), U1172.1 (~RESET)
EXT_D_N: U904.14 (SBU2), U907.14 (S4)
EXT_D_P: U904.15 (SBU1), U907.10 (S3)
EXT_ORIENT: R1185.1, U903.9 (SEL), U1172.4 (P2)
EXT_RX_N: U903.8 (A1N), U906.18 (B0N)
EXT_RX_P: U903.7 (A1P), U906.19 (B0P)
EXT_SCL: R902.2, U905.6 (SCL), U1131.13 (SC5)
EXT_SDA: R903.2, U905.7 (SDA), U1131.12 (SD5)
EXT_TX_N: U903.4 (A0N), U906.16 (B1N)
EXT_TX_P: U903.3 (A0P), U906.17 (B1P)
EXT_VBUS: C1904.1, J901.A4 (VBUS), J901.A9 (VBUS), J901.B4 (VBUS), J901.B9 (VBUS), Q1004.3 (D), R231.1, R1906.1, U905.2 (VBUS), U1902.5 (IN)
GND: C201.2, C202.2, C203.2, C204.2, C205.2, C206.2, C207.2, C208.2, C209.2, C210.2, C211.2, C212.2, C213.2, C214.2, C215.2, C216.2, C217.2, C218.2, C219.2, C220.2, C221.2, C224.2, C226.2, C403.2, C404.2, C405.2, C406.2, C407.2, C408.2, C409.2, C410.2, C411.2, C503.2, C504.2, C505.2, C506.2, C507.2, C508.2, C509.2, C510.2, C511.2, C603.2, C604.2, C605.2, C606.2, C607.2, C608.2, C609.2, C610.2, C611.2, C703.2, C704.2, C705.2, C706.2, C707.2, C708.2, C709.2, C710.2, C711.2, C803.2, C804.2, C805.2, C806.2, C807.2, C808.2, C809.2, C810.2, C811.2, C902.2, C903.2, C904.2, C905.2, C906.2, C907.2, C908.2, C909.2, C910.2, C1001.2, C1002.2, C1003.2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
HOST_BUDGET_22K: Q1912.1 (G), R1917.1, U1182.4 (QE)
HOST_BUDGET_68K: Q1911.1 (G), R1915.1, U1182.3 (QD)
HOST_BUDGET_FAULT_N: R1912.2, U1101.1 (GPIO4), U1901.4 (FAULT_N)
HOST_EXT: Q902.1 (G), R906.1, U1182.7 (QH)
HOST_TARGET_5V: C1220.1, C1320.1, C1420.1, C1520.1, C1620.1, C1912.1, C1913.1, R1211.1, R1311.1, R1411.1, R1511.1, R1611.1, U1202.5 (IN), U1302.5 (IN), U1402.5 (IN), U1502.5 (IN), U1602.5 (IN), U1901.6 (OUT)
HOST_TARGET_EN: R1911.1, U1182.5 (QF), U1901.3 (EN)
HUB_D_N: U201.90 (USB2UP_DM), U907.3 (D1), U907.13 (D4)
HUB_D_P: U201.89 (USB2UP_DP), U907.6 (D2), U907.9 (D3)
HUB_RUN: R1173.2, U204.2, U1172.7 (P4)
HUB_RX_N: U201.94 (USB3UP_RXDP), U906.4 (A0N)
HUB_RX_P: U201.95 (USB3UP_RXDM), U906.3 (A0P)
HUB_SCL: R228.1, U201.75 (PF26/SLV_I2C_CLK), U1131.15 (SC6)
HUB_SDA: R229.1, U201.76 (PF27/SLV_I2C_DATA), U1131.14 (SD6)
HUB_TX_N: C223.2, U906.8 (A1N)
HUB_TX_P: C222.2, U906.7 (A1P)
HUB_UP_VBUS: U201.2 (PF30/VBUS_MON_UP), U205.4
HV_CHARGE: C1007.1, C1008.1, C1009.1, C1010.1, C1230.1, C1231.1, C1232.1, C1233.1, C1235.1, C1330.1, C1331.1, C1332.1, C1333.1, C1335.1, C1430.1, C1431.1, C1432.1, C1433.1, C1435.1, C1530.1, C1531.1, C1532.1, C1533.1, C1535.1, C1630.1, C1631.1, C1632.1, C1633.1, C1635.1, C2002.1, Q1002.5 (D), Q1230.5 (D), Q1330.5 (D), Q1430.5 (D), Q1530.5 (D), Q1630.5 (D), R1019.1, R1021.1, R1027.1, R1156.1, R2001.1, TP1002.1 (1_1), U1004.10 (VIN), U1004.11 (VIN), U1004.12 (VIN), U1230.3 (VIN), U1330.3 (VIN), U1430.3 (VIN), U1530.3 (VIN), U1630.3 (VIN), U2001.1 (IN), U2001.2 (IN)
INPUT_PROTECT_FAULT_N: R1006.2, U1003.14 (~FLT), U1172.8 (P5)
LED_DATA: U1101.20 (GPIO20), U1171.2
LOGIC_OVLO: Q1004.2 (S), R1907.2, R1908.1, U1902.2 (OVLO)
MCU_I2C_SCL: R1132.2, U1101.26 (GPIO25), U1131.19 (SCL), U1172.12 (SCL)
MCU_I2C_SDA: R1131.2, U1101.25 (GPIO24), U1131.20 (SDA), U1172.13 (SDA)
MCU_UART_RX: J1132.1, R1135.2, U1101.78 (GPIO1)
MCU_UART_TX: J1132.3, R1112.2, U1101.77 (GPIO0)
MCU_USB_D_N: R1105.2, TP1101.1 (1_1), U201.41 (USB2DN_DM6/PRT_DIS_M6)
MCU_USB_D_P: R1106.2, TP1102.1 (1_1), U201.42 (USB2DN_DP6/PRT_DIS_P6)
unnamed: C1002.1, R1007.1, U1003.15 (OUT), U1003.16 (OUT)
unnamed: C1006.2, R1013.1
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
